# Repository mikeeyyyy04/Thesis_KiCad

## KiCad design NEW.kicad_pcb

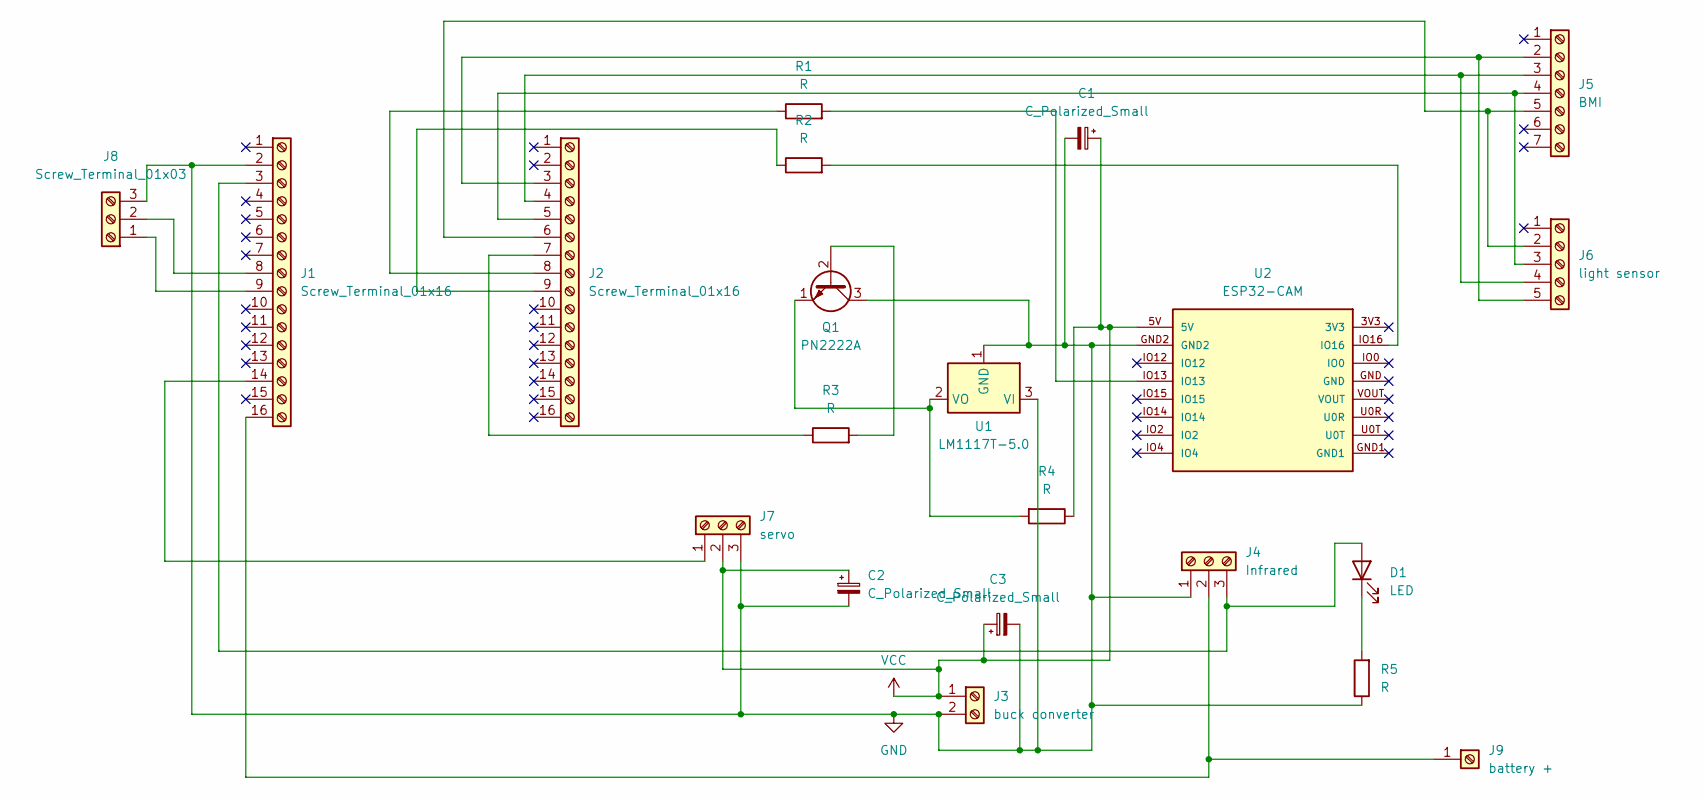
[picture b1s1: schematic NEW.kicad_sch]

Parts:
C1, C2, C3: C_Polarized_Small; C_Disc_D3.8mm_W2.6mm_P2.50mm
D1: LED; PinHeader_1x02_P2.54mm_Vertical
J1, J2: Screw_Terminal_01x16; PinHeader_1x16_P2.54mm_Vertical
J3: buck converter; PinHeader_1x02_P2.54mm_Vertical
J4: Infrared; PinHeader_1x03_P2.54mm_Vertical
J5: BMI; PinHeader_1x07_P2.00mm_Vertical
J6: light sensor; PinHeader_1x05_P2.00mm_Vertical
J7: servo; PinHeader_1x03_P2.54mm_Vertical
J8: Screw_Terminal_01x03; PinHeader_1x03_P2.54mm_Vertical
J9: battery +; PinHeader_1x01_P2.54mm_Vertical
Q1: PN2222A; TO-92_Inline
R1, R2, R3, R4, R5: R; R_Axial_DIN0207_L6.3mm_D2.5mm_P7.62mm_Horizontal
U1: LM1117T-5.0; TO-220-3_Horizontal_TabDown
U2: ESP32-CAM

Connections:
GND: C1.2, C2.2, C3.2, J1.2, J3.2, J4.1, J7.3, J8.3, Q1.3 (C), R5.1, U1.1 (GND), U1.3 (VI), U2.GND2
unnamed: D1.2 (A), J1.3, J4.3
unnamed: D1.1 (K), R5.2
unnamed: J1.8, J8.2
unnamed: J1.9, J8.1
unnamed: J1.14, J7.1
unnamed: J1.16, J4.2, J9.1
unnamed: J2.3, J5.2, J6.5
unnamed: J2.4, J5.3, J6.4
unnamed: J2.5, J5.4, J6.3
unnamed: J2.6, J5.5, J6.2
unnamed: J2.7, R3.1
unnamed: J2.8, R1.1
unnamed: J2.9, R2.1
unnamed: Q1.2 (B), R3.2
unnamed: Q1.1 (E), R4.2, U1.2 (VO)
unnamed: R1.2, U2.IO13
unnamed: R2.2, U2.IO16
VCC: C1.1, C2.1, C3.1, J3.1, J7.2, R4.1, U2.5V

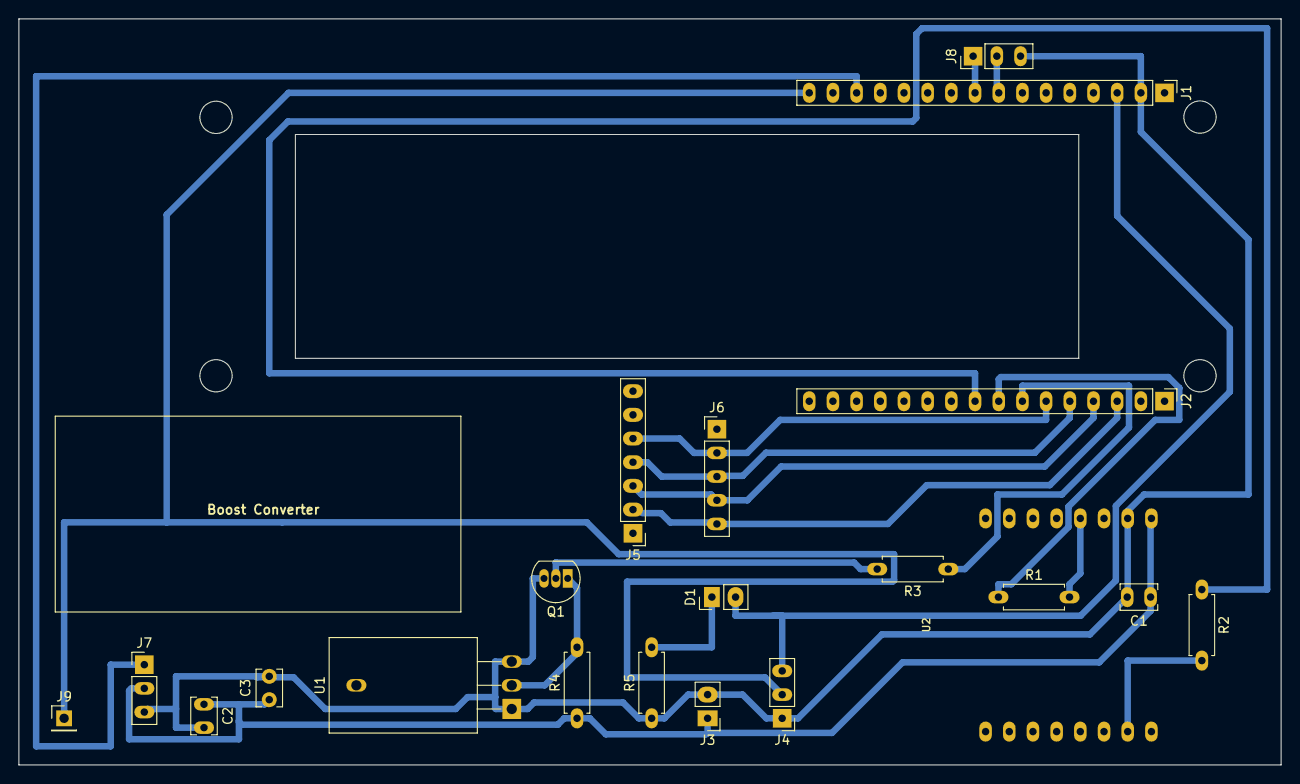
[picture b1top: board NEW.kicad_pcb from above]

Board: 2 copper layers, 135.3 x 80.0 mm, 21 parts (0 on the bottom side), 19 nets.

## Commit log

2026-04-01 Initial KiCad project commit
2026-04-06 added mounting holes
2026-04-06 added silkscreen for boost converter
2026-04-07 chore: update project files
2026-04-10 Update KiCad project files
